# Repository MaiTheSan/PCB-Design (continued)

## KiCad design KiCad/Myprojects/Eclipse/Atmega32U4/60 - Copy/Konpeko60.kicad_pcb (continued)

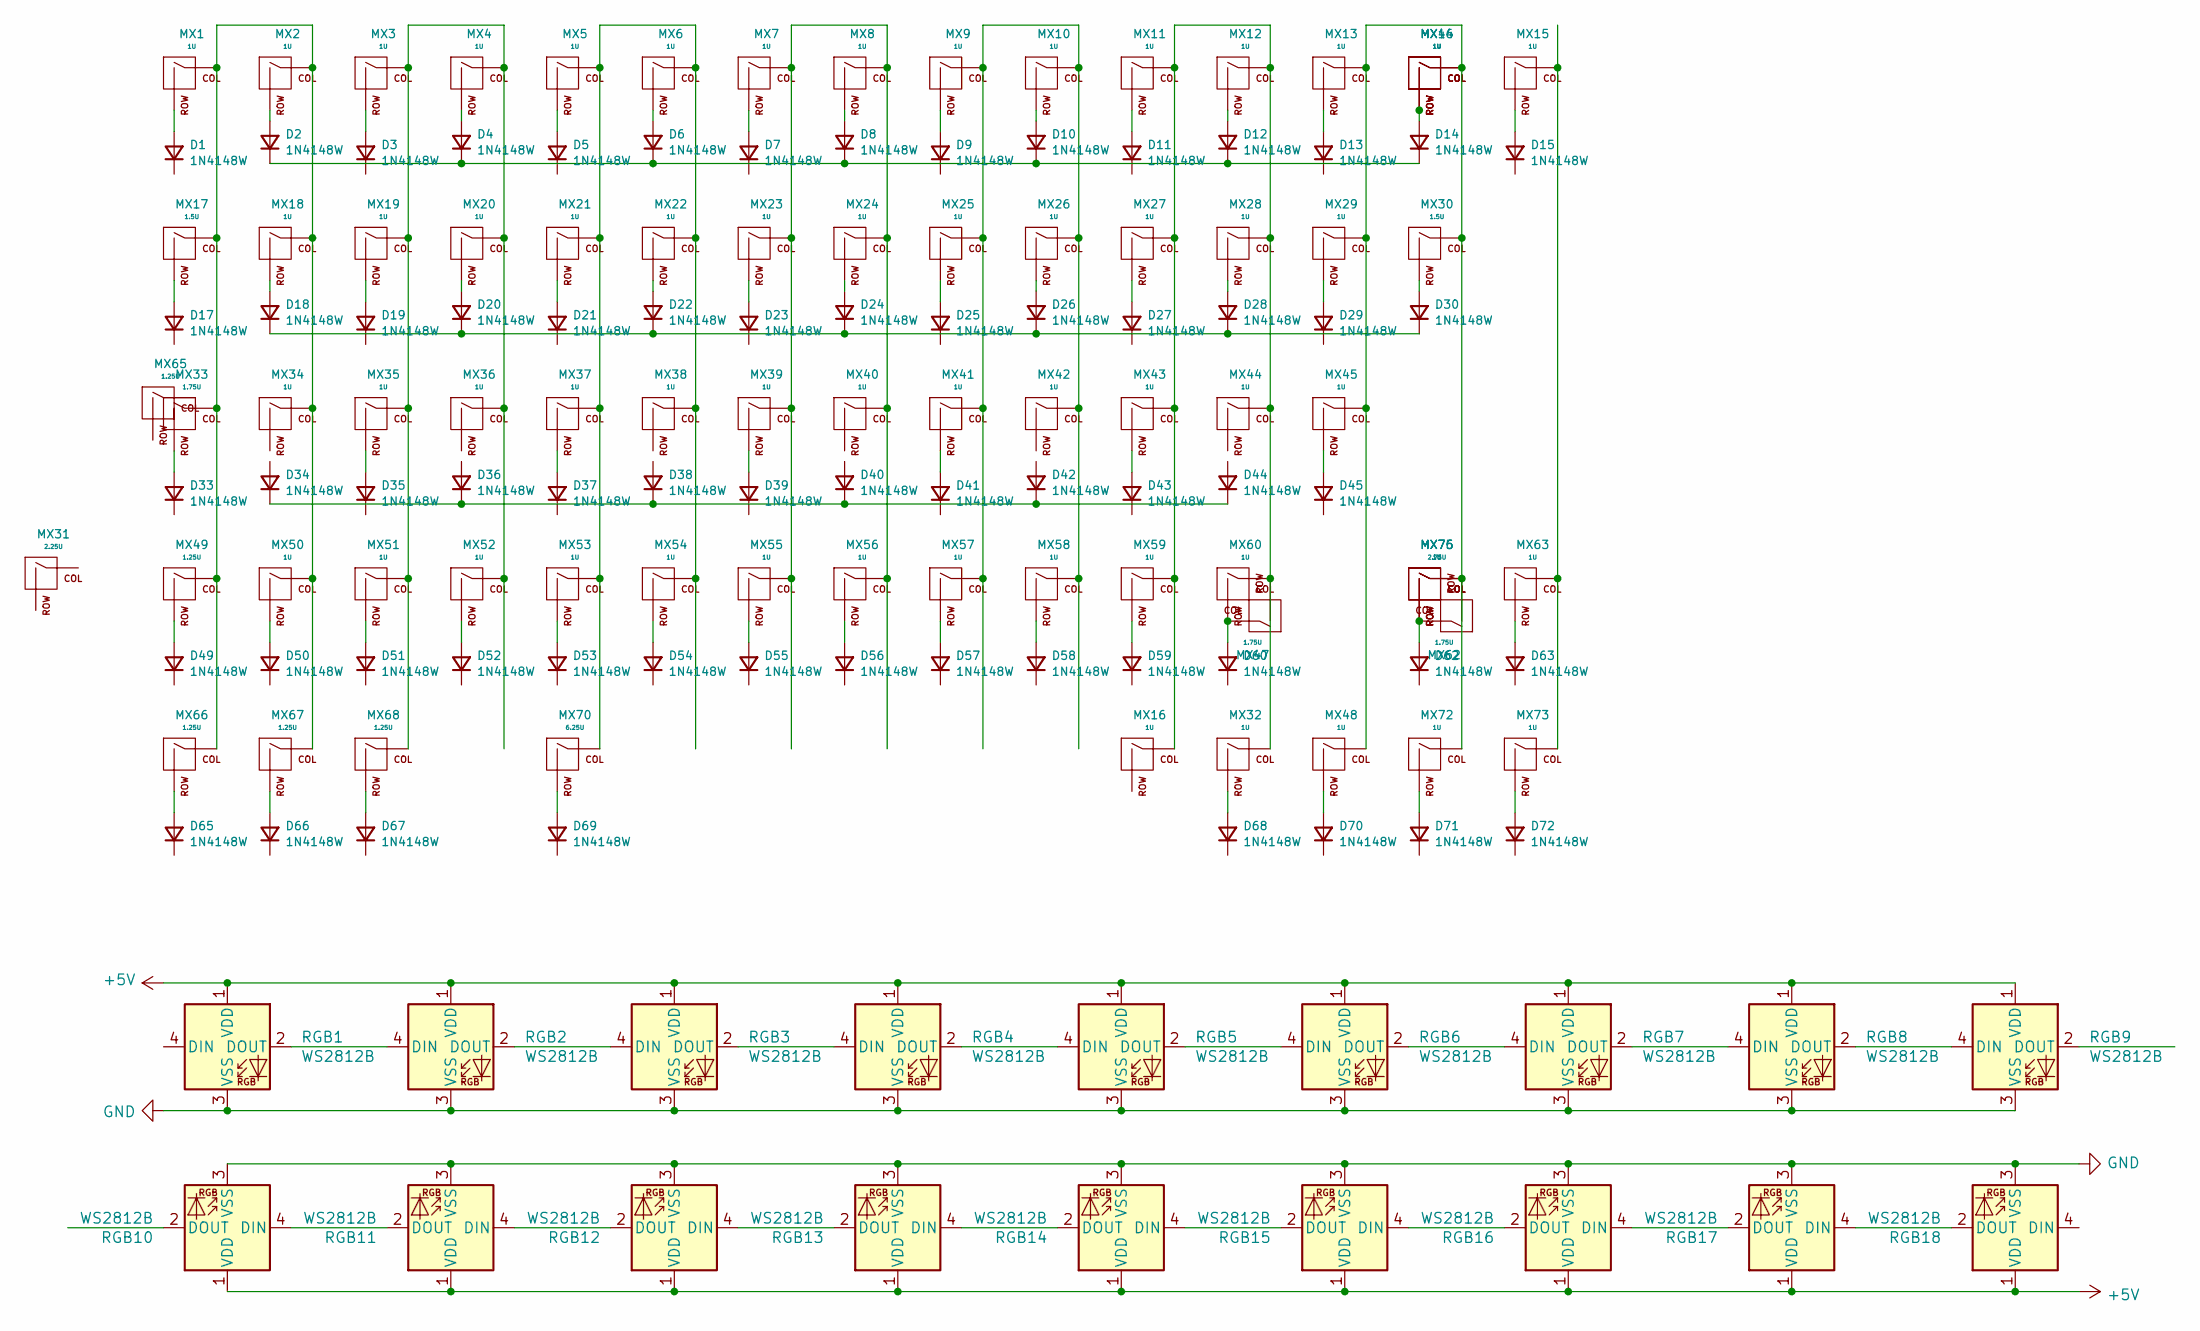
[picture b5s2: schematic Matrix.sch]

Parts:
D1, D2, D3, D4, D5, D6, D7, D8, D9, D10, D11, D12, D13, D14, D15, D17, D18, D19, D20, D21, D22, D23, D24, D25, D26, D27, D28, D29, D30, D33, D34, D35, D36, D37, D38, D39, D40, D41, D42, D43, D44, D45, D49, D50, D51, D52, D53, D54, D55, D56, D57, D58, D59, D60, D62, D63, D65, D66, D67, D68, D69, D70, D71, D72: 1N4148W; DIODE_1206_SawnsProjects
MX1, MX2, MX3, MX4, MX5, MX6, MX7, MX8, MX9, MX10, MX11, MX12, MX13, MX14, MX15, MX16, MX18, MX19, MX20, MX21, MX22, MX23, MX24, MX25, MX26, MX27, MX28, MX29, MX32, MX34, MX35, MX36, MX37, MX38, MX39, MX40, MX41, MX42, MX43, MX44, MX45, MX48, MX50, MX51, MX52, MX53, MX54, MX55, MX56, MX57, MX58, MX59, MX60, MX63, MX72, MX73, MX75: 1U; MXOnly-1U-NoLED
MX17, MX30: 1.5U; MXOnly-1.5U-NoLED
MX31: 2.25U; MXOnly-2.25U-NoLED
MX33, MX47, MX62: 1.75U; MXOnly-1.75U-NoLED
MX46: 1U; MXOnly-2U-NoLED
MX49, MX65, MX66, MX67, MX68: 1.25U; MXOnly-1.25U-NoLED
MX70: 6.25U; MXOnly-6.25U-ReversedStabilizers-NoLED
MX76: 2.75U; MXOnly-2.75U-NoLED
RGB1, RGB2, RGB3, RGB4, RGB5, RGB6, RGB7, RGB8, RGB9, RGB10, RGB11, RGB12, RGB13, RGB14, RGB15, RGB16, RGB17, RGB18: WS2812B; LED_WS2812B_PLCC4_5.0x5.0mm_P3.2mm

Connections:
+5V: RGB1.1 (VDD), RGB2.1 (VDD), RGB3.1 (VDD), RGB4.1 (VDD), RGB5.1 (VDD), RGB6.1 (VDD), RGB7.1 (VDD), RGB8.1 (VDD), RGB9.1 (VDD), RGB10.1 (VDD), RGB11.1 (VDD), RGB12.1 (VDD), RGB13.1 (VDD), RGB14.1 (VDD), RGB15.1 (VDD), RGB16.1 (VDD), RGB17.1 (VDD), RGB18.1 (VDD); also elsewhere on the board
GND: RGB1.3 (VSS), RGB2.3 (VSS), RGB3.3 (VSS), RGB4.3 (VSS), RGB5.3 (VSS), RGB6.3 (VSS), RGB7.3 (VSS), RGB8.3 (VSS), RGB9.3 (VSS), RGB10.3 (VSS), RGB11.3 (VSS), RGB12.3 (VSS), RGB13.3 (VSS), RGB14.3 (VSS), RGB15.3 (VSS), RGB16.3 (VSS), RGB17.3 (VSS), RGB18.3 (VSS); also elsewhere on the board
unnamed: D1.2 (A), MX1.2 (ROW)
unnamed: D2.2 (A), MX2.2 (ROW)
unnamed: D3.2 (A), MX3.2 (ROW)
unnamed: D4.2 (A), MX4.2 (ROW)
unnamed: D5.2 (A), MX5.2 (ROW)
unnamed: D6.2 (A), MX6.2 (ROW)
unnamed: D7.2 (A), MX7.2 (ROW)
unnamed: D8.2 (A), MX8.2 (ROW)
unnamed: D9.2 (A), MX9.2 (ROW)
unnamed: D10.2 (A), MX10.2 (ROW)
unnamed: D11.2 (A), MX11.2 (ROW)
unnamed: D12.2 (A), MX12.2 (ROW)
unnamed: D13.2 (A), MX13.2 (ROW)
unnamed: D14.2 (A), MX14.2 (ROW), MX46.2 (ROW)
unnamed: D15.2 (A), MX15.2 (ROW)
unnamed: D17.2 (A), MX17.2 (ROW)
unnamed: D18.2 (A), MX18.2 (ROW)
unnamed: D19.2 (A), MX19.2 (ROW)
unnamed: D20.2 (A), MX20.2 (ROW)
unnamed: D21.2 (A), MX21.2 (ROW)
unnamed: D22.2 (A), MX22.2 (ROW)
unnamed: D23.2 (A), MX23.2 (ROW)
unnamed: D24.2 (A), MX24.2 (ROW)
unnamed: D25.2 (A), MX25.2 (ROW)
unnamed: D26.2 (A), MX26.2 (ROW)
unnamed: D27.2 (A), MX27.2 (ROW)
unnamed: D28.2 (A), MX28.2 (ROW)
unnamed: D29.2 (A), MX29.2 (ROW)
unnamed: D30.2 (A), MX30.2 (ROW)
unnamed: D33.2 (A), MX33.2 (ROW)
unnamed: D35.2 (A), MX35.2 (ROW)
unnamed: D37.2 (A), MX37.2 (ROW)
unnamed: D39.2 (A), MX39.2 (ROW)
unnamed: D41.2 (A), MX41.2 (ROW)
unnamed: D43.2 (A), MX43.2 (ROW)
unnamed: D45.2 (A), MX45.2 (ROW)
unnamed: D49.2 (A), MX49.2 (ROW)
unnamed: D50.2 (A), MX50.2 (ROW)
unnamed: D51.2 (A), MX51.2 (ROW)
unnamed: D52.2 (A), MX52.2 (ROW)
unnamed: D53.2 (A), MX53.2 (ROW)
unnamed: D54.2 (A), MX54.2 (ROW)
unnamed: D55.2 (A), MX55.2 (ROW)
unnamed: D56.2 (A), MX56.2 (ROW)
unnamed: D57.2 (A), MX57.2 (ROW)
unnamed: D58.2 (A), MX58.2 (ROW)
unnamed: D59.2 (A), MX59.2 (ROW)
unnamed: D60.2 (A), MX47.1 (COL), MX60.2 (ROW)
unnamed: D62.2 (A), MX62.1 (COL), MX75.2 (ROW), MX76.2 (ROW)
unnamed: D63.2 (A), MX63.2 (ROW)
unnamed: D65.2 (A), MX66.2 (ROW)
unnamed: D66.2 (A), MX67.2 (ROW)
unnamed: D67.2 (A), MX68.2 (ROW)
unnamed: D68.2 (A), MX32.2 (ROW)
unnamed: D69.2 (A), MX70.2 (ROW)
unnamed: D70.2 (A), MX48.2 (ROW)
unnamed: D71.2 (A), MX72.2 (ROW)
unnamed: D72.2 (A), MX73.2 (ROW)
unnamed: MX1.1 (COL), MX2.1 (COL), MX17.1 (COL), MX18.1 (COL), MX33.1 (COL), MX34.1 (COL), MX49.1 (COL), MX50.1 (COL), MX66.1 (COL), MX67.1 (COL)
unnamed: MX9.1 (COL), MX10.1 (COL), MX25.1 (COL), MX26.1 (COL), MX41.1 (COL), MX42.1 (COL), MX57.1 (COL), MX58.1 (COL)
unnamed: MX11.1 (COL), MX12.1 (COL), MX16.1 (COL), MX27.1 (COL), MX28.1 (COL), MX32.1 (COL), MX43.1 (COL), MX44.1 (COL), MX47.2 (ROW), MX59.1 (COL), MX60.1 (COL)
unnamed: MX13.1 (COL), MX14.1 (COL), MX29.1 (COL), MX30.1 (COL), MX45.1 (COL), MX46.1 (COL), MX48.1 (COL), MX62.2 (ROW), MX72.1 (COL), MX75.1 (COL), MX76.1 (COL)
unnamed: MX15.1 (COL), MX63.1 (COL), MX73.1 (COL)
unnamed: MX3.1 (COL), MX4.1 (COL), MX19.1 (COL), MX20.1 (COL), MX35.1 (COL), MX36.1 (COL), MX51.1 (COL), MX52.1 (COL), MX68.1 (COL)
unnamed: MX5.1 (COL), MX6.1 (COL), MX21.1 (COL), MX22.1 (COL), MX37.1 (COL), MX38.1 (COL), MX53.1 (COL), MX54.1 (COL), MX70.1 (COL)
unnamed: MX7.1 (COL), MX8.1 (COL), MX23.1 (COL), MX24.1 (COL), MX39.1 (COL), MX40.1 (COL), MX55.1 (COL), MX56.1 (COL)
unnamed: RGB1.2 (DOUT), RGB2.4 (DIN)
unnamed: RGB2.2 (DOUT), RGB3.4 (DIN)
unnamed: RGB3.2 (DOUT), RGB4.4 (DIN)
unnamed: RGB4.2 (DOUT), RGB5.4 (DIN)
unnamed: RGB5.2 (DOUT), RGB6.4 (DIN)
unnamed: RGB6.2 (DOUT), RGB7.4 (DIN)
unnamed: RGB7.2 (DOUT), RGB8.4 (DIN)
unnamed: RGB8.2 (DOUT), RGB9.4 (DIN)
unnamed: RGB10.4 (DIN), RGB11.2 (DOUT)
unnamed: RGB11.4 (DIN), RGB12.2 (DOUT)
unnamed: RGB12.4 (DIN), RGB13.2 (DOUT)
unnamed: RGB13.4 (DIN), RGB14.2 (DOUT)
unnamed: RGB14.4 (DIN), RGB15.2 (DOUT)
unnamed: RGB15.4 (DIN), RGB16.2 (DOUT)
unnamed: RGB16.4 (DIN), RGB17.2 (DOUT)
unnamed: RGB17.4 (DIN), RGB18.2 (DOUT)

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
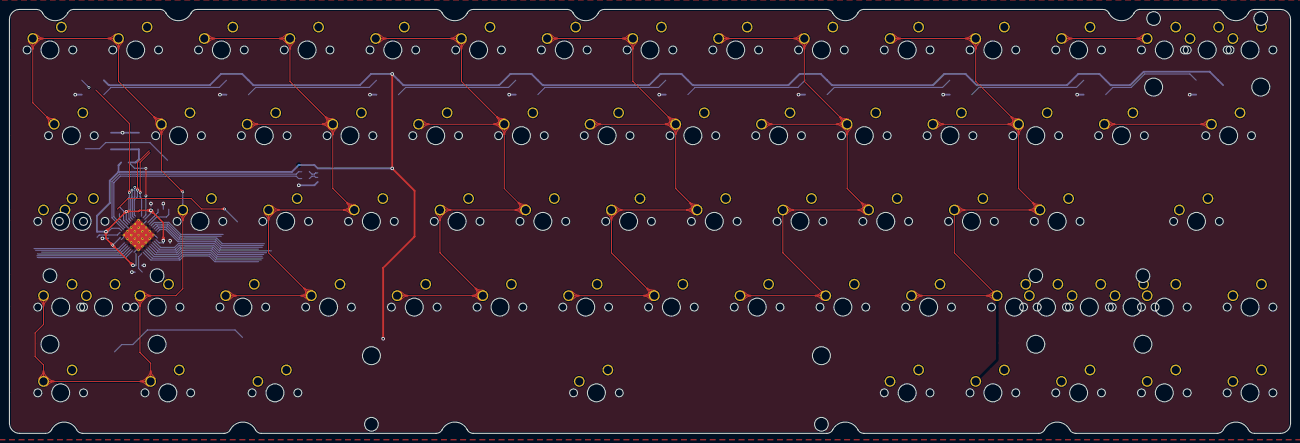
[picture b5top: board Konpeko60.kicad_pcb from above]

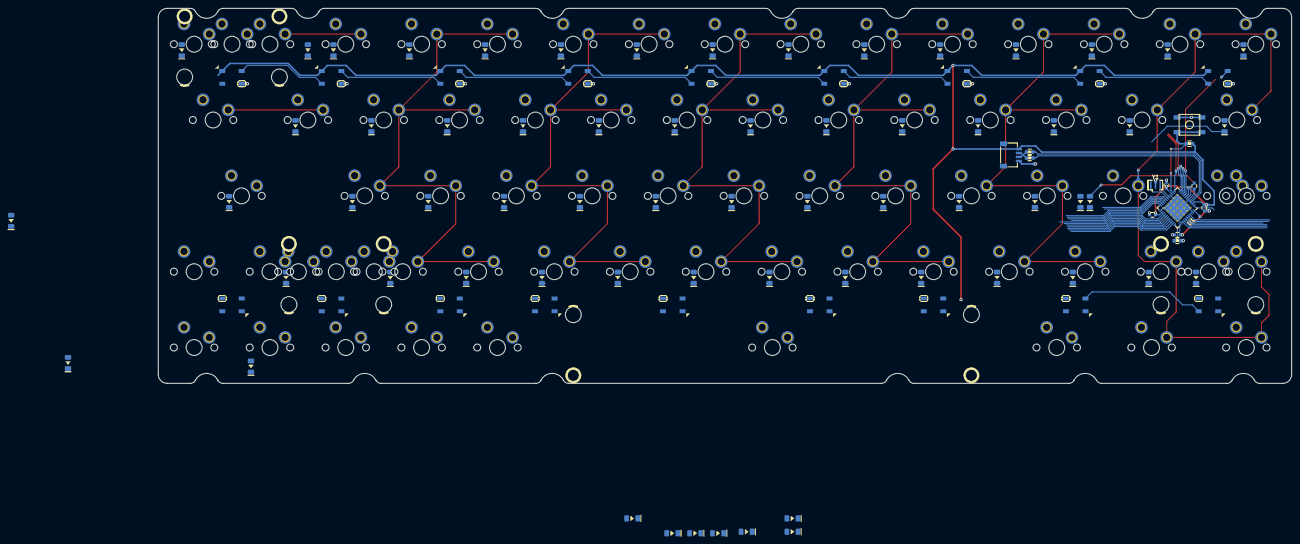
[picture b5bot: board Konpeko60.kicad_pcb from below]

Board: 2 copper layers, 284.7 x 94.2 mm, 166 parts (95 on the bottom side), 93 nets.
